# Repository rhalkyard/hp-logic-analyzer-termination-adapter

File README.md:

# Termination Adapter for HP Logic Analyzers

The PCB in this repo is a quick and dirty clone of the HP 01650-63203
termination adapter, used for direct connection of a 40-pin pod cable to a
dedicated test port, providing a passive termination network to minimise loading
on the device under test. By adding a cheap set of hookup leads and
minigrabbers, it can also serve as a DIY replacement for the probe pods that are
so frequently missing from analzyers that crop up on the used market.

## Termination network

Per HP application note [AP1244 "Minimizing Intrusion Effects when Probing with
a Logic Analyzer"](docs/5962-8620E_AP1244-1_Minimizing_Intrusion_Effects_When_Probing_With_a_Logic_Analyzer_Jul95),
each probe must be terminated with a series RC network as below (from Figure 1):

HP sold arrays of this termination network (1810-1278 for 9 networks in a DIP
package, 1810-1588 for 5 networks in a SIP package). Naturally these are either
NLA or not available for purchase by mere mortals, but it's easy enough to
implement it in discrete components.

## Pinouts

## Power

The logic analyzer supplies +5V at 600mA to each pod connector on pins 1 and 39
of the 40-pin connector. The 01650-63203 termination adatper brings this supply
out to pin 1 of the 20-pin connector. Per HP's documentation, this is intended
solely for powering active probe hardware, and must be a no-connect on the
device under test.

For safety, on this adapter, the +5V supply is broken by a solder jumper that
must be closed in order to supply +5V to the 20 pin connector.

## BOM and assembly

Each adapter requires the following

| Quantity     | Component                                                   |
|--------------|-------------------------------------------------------------|
| 18           | Capacitor, 8pF, 0402 footprint                              |
| 18           | Resistor, 250 ohm 1%, 0402 footprint                        |
| 18           | Resistor, 90.9K 1%, 0402 footprint                          |
| 1            | Keyed 0.1" PCB header, 2x20 pin, right angle                |
| 1            | Keyed 0.1" PCB header, 2x10 pin, vertical                   |
| 1 (optional) | 20 pin IDC ribbon cable, length to taste, female connectors |

Conveniently, JLCPCB's minimum order quantity of 5 is exactly the number of pods
required for my 1652B analyzer. I ordered a set of 5 boards with SMD components
preassembled for approximately 25 USD.

The original 01650-63203 adapters had an exposed section of flexible PCB,
terminated in a 20 pin IDC receptacle, designed to directly connect to a
board-mounted header on the DUT. This adapter substitutes this with a header - a
short length of ribbon cable can be used to connect to the DUT, or standard
Dupont leads can be connected to the pins for individual probes.

## (Lack of) Warranty

This project is presented on an as-is, 'works for me' basis. You are welcome to
build it, use it, adapt it to your own purposes, but all at your own risk.

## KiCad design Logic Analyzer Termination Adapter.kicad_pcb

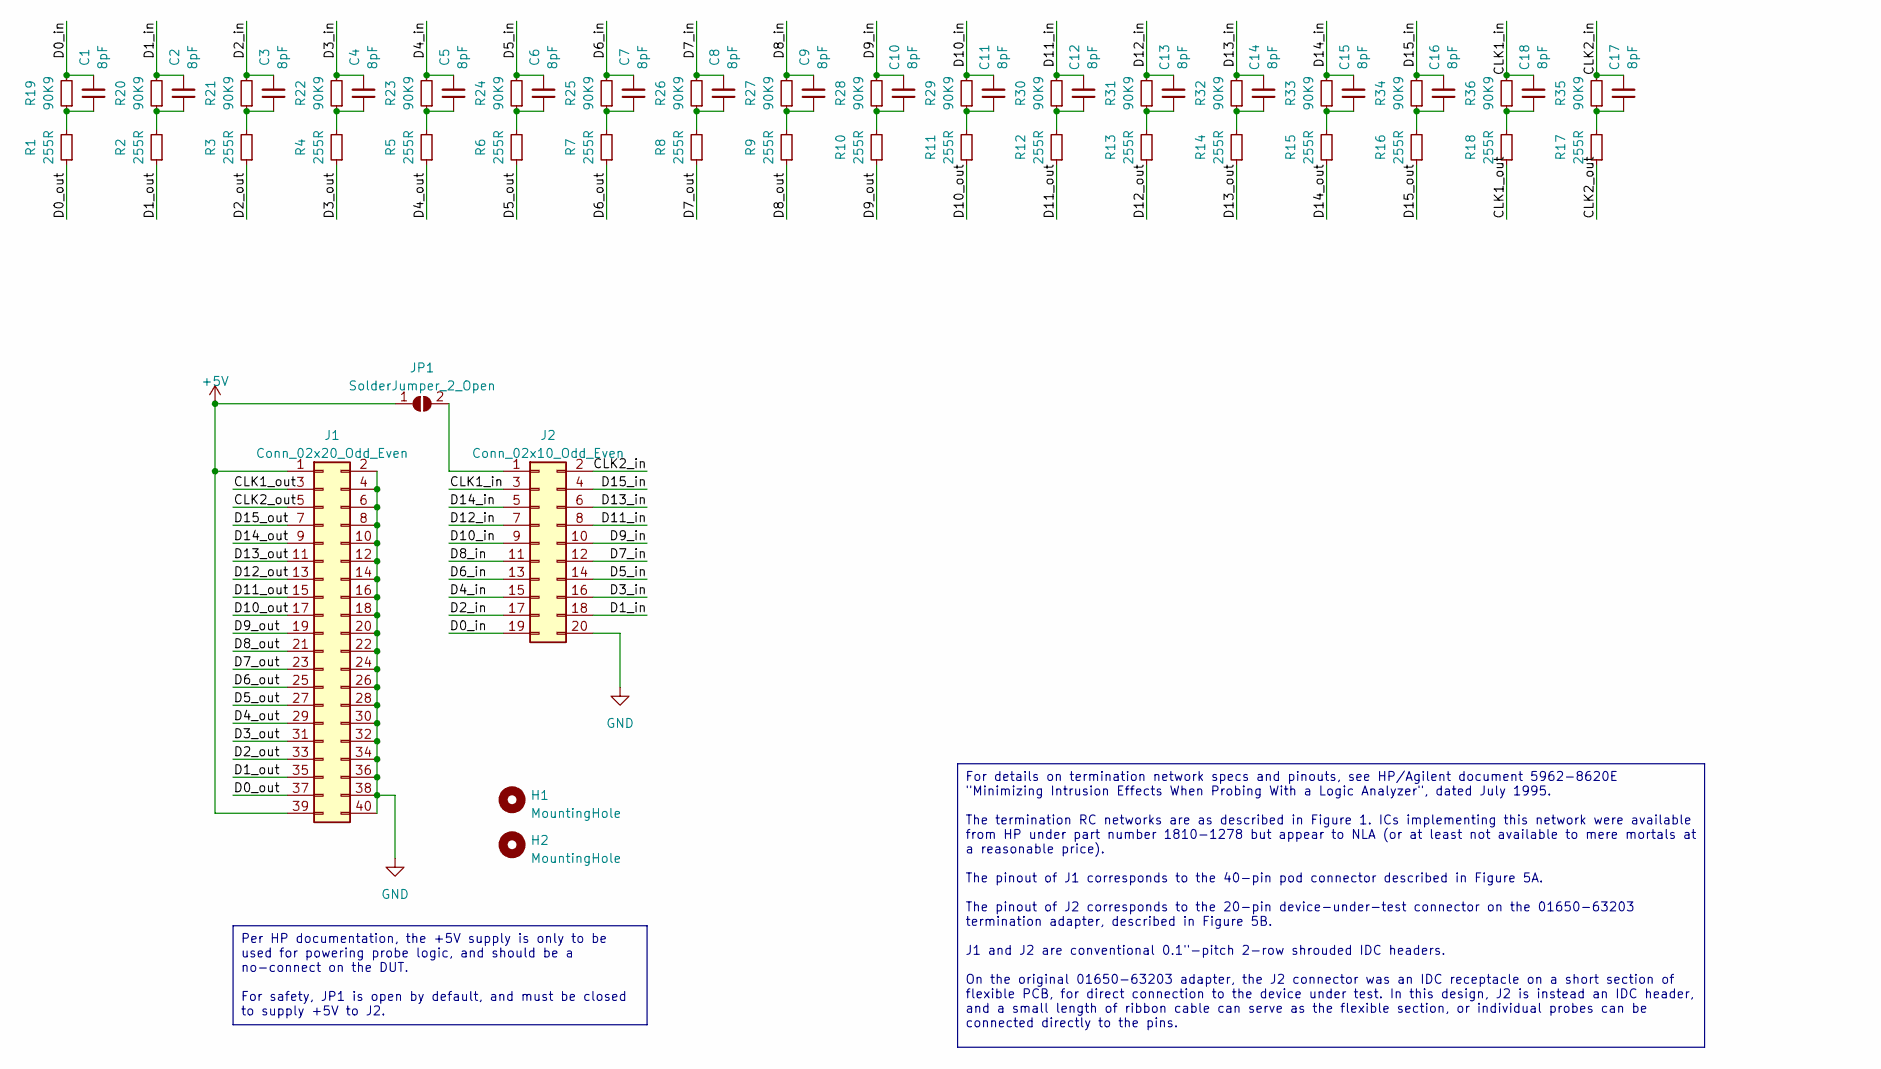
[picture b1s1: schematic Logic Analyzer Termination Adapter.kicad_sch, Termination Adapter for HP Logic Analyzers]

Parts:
C1, C2, C3, C4, C5, C6, C7, C8, C9, C10, C11, C12, C13, C14, C15, C16, C17, C18: 8pF; C_0402_1005Metric_Pad0.74x0.62mm_HandSolder; LCSC C880622
H1, H2: MountingHole; MountingHole_2.7mm_M2.5
J1: Conn_02x20_Odd_Even; IDC-Header_2x20_P2.54mm_Horizontal; MPN BHR-40-HUA
J2: Conn_02x10_Odd_Even; IDC-Header_2x10_P2.54mm_Vertical; MPN 302-S201
JP1: SolderJumper_2_Open; SolderJumper-2_P1.3mm_Open_RoundedPad1.0x1.5mm
R1, R2, R3, R4, R5, R6, R7, R8, R9, R10, R11, R12, R13, R14, R15, R16, R17, R18: 255R; R_0402_1005Metric_Pad0.72x0.64mm_HandSolder; LCSC C226375
R19, R20, R21, R22, R23, R24, R25, R26, R27, R28, R29, R30, R31, R32, R33, R34, R35, R36: 90K9; R_0402_1005Metric_Pad0.72x0.64mm_HandSolder; LCSC C2998102

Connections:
+5V: J1.1, J1.39, JP1.1 (A)
/CLK1_in: C18.2, J2.3, R36.2
/CLK1_out: J1.3, R18.1
/CLK2_in: C17.2, J2.2, R35.2
/CLK2_out: J1.5, R17.1
/D0_in: C1.2, J2.19, R19.2
/D0_out: J1.37, R1.1
/D1_in: C2.2, J2.18, R20.2
/D1_out: J1.35, R2.1
/D2_in: C3.2, J2.17, R21.2
/D2_out: J1.33, R3.1
/D3_in: C4.2, J2.16, R22.2
/D3_out: J1.31, R4.1
/D4_in: C5.2, J2.15, R23.2
/D4_out: J1.29, R5.1
/D5_in: C6.2, J2.14, R24.2
/D5_out: J1.27, R6.1
/D6_in: C7.2, J2.13, R25.2
/D6_out: J1.25, R7.1
/D7_in: C8.2, J2.12, R26.2
/D7_out: J1.23, R8.1
/D8_in: C9.2, J2.11, R27.2
/D8_out: J1.21, R9.1
/D9_in: C10.2, J2.10, R28.2
/D9_out: J1.19, R10.1
/D10_in: C11.2, J2.9, R29.2
/D10_out: J1.17, R11.1
/D11_in: C12.2, J2.8, R30.2
/D11_out: J1.15, R12.1
/D12_in: C13.2, J2.7, R31.2
/D12_out: J1.13, R13.1
/D13_in: C14.2, J2.6, R32.2
/D13_out: J1.11, R14.1
/D14_in: C15.2, J2.5, R33.2
/D14_out: J1.9, R15.1
/D15_in: C16.2, J2.4, R34.2
/D15_out: J1.7, R16.1
GND: J1.2, J1.4, J1.6, J1.8, J1.10, J1.12, J1.14, J1.16, J1.18, J1.20, J1.22, J1.24, J1.26, J1.28, J1.30, J1.32, J1.34, J1.36, J1.38, J1.40, J2.20
unnamed: C1.1, R1.2, R19.1
unnamed: C2.1, R2.2, R20.1
unnamed: C3.1, R3.2, R21.1
unnamed: C4.1, R4.2, R22.1
unnamed: C5.1, R5.2, R23.1
unnamed: C6.1, R6.2, R24.1
unnamed: C7.1, R7.2, R25.1
unnamed: C8.1, R8.2, R26.1
unnamed: C9.1, R9.2, R27.1
unnamed: C10.1, R10.2, R28.1
unnamed: C11.1, R11.2, R29.1
unnamed: C12.1, R12.2, R30.1
unnamed: C13.1, R13.2, R31.1
unnamed: C14.1, R14.2, R32.1
unnamed: C15.1, R15.2, R33.1
unnamed: C16.1, R16.2, R34.1
unnamed: C17.1, R17.2, R35.1
unnamed: C18.1, R18.2, R36.1
unnamed: J2.1, JP1.2 (B)

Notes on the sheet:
Per HP documentation, the +5V supply is only to be used for powering probe logic, and should be a no-connect on the DUT. For safety, JP1 is open by default, and must be closed to supply +5V to J2.
For details on termination network specs and pinouts, see HP/Agilent document 5962-8620E "Minimizing Intrusion Effects When Probing With a Logic Analyzer", dated July 1995. The termination RC networks are as described in Figure 1. ICs implementing this network were available from HP under part numb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

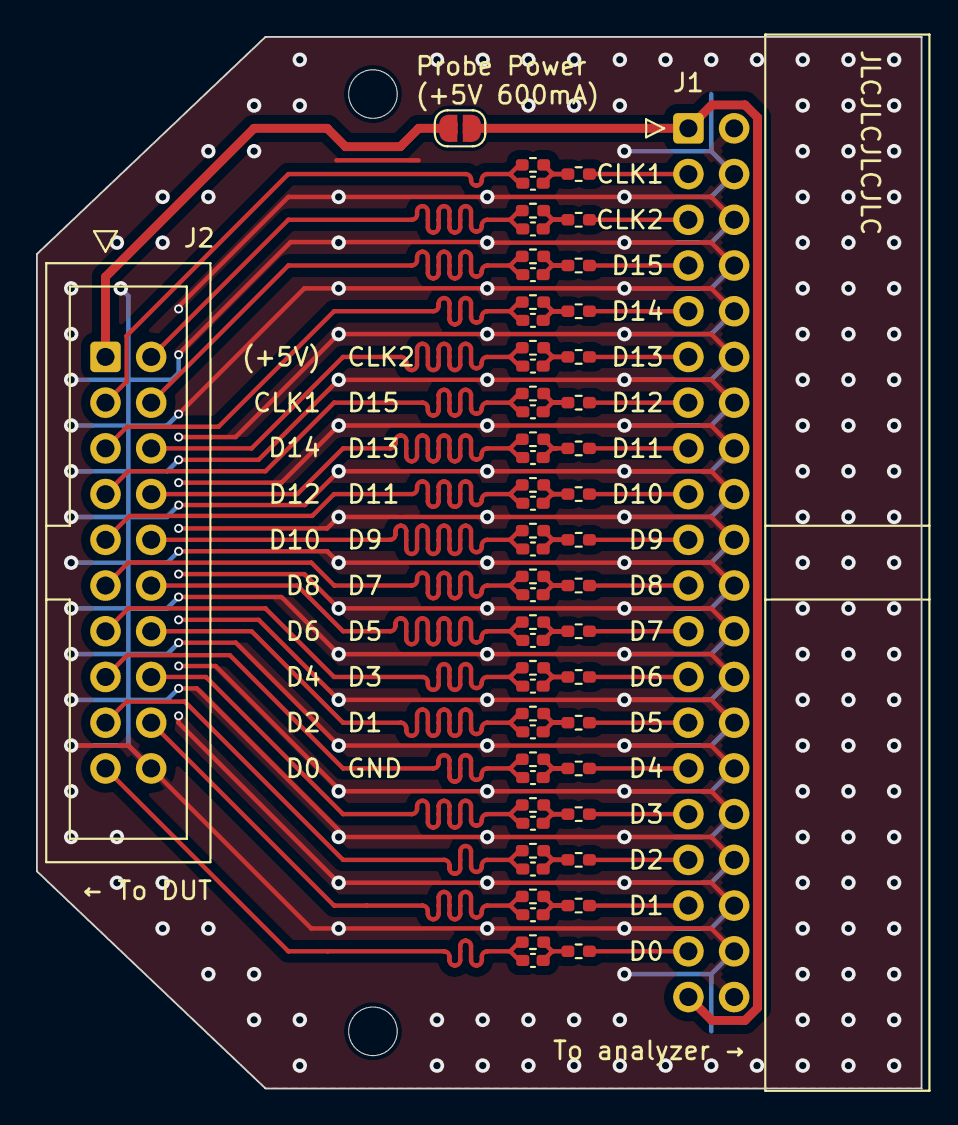
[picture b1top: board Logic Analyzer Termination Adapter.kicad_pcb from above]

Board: 2 copper layers, 49.1 x 58.4 mm, 59 parts (0 on the bottom side), 57 nets.
